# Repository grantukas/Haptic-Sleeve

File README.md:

# Haptic-Sleeve
Repository for the code used for the Haptic Sleeve Project!

Below is a brief description of the folders.

### CaseModels
Contains the 3D models that house the Haptic Sleeve PCB.

### ESP32 Code
Contains the Micropython code to run on the ESP32, along with Micropython firmware to flash (.bin file).

### Haptic Sleeve Testing Program
Contains the testing program and documentation for testing the Haptic Sleeve. The data extraction program (to convert log file data to CSV) also lives here.

### Learn To Write Code
Contains the code for the Learn To Write Software.

### Schematic+Board
Contains the schematic and board layout files for the Haptic Sleeve.

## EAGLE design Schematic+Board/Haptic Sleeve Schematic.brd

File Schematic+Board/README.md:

## Schematic and board layout files
Schematic and board layout for the ESP32, 2 Sparkfun motor drivers.
Created in Autodesk Eagle.

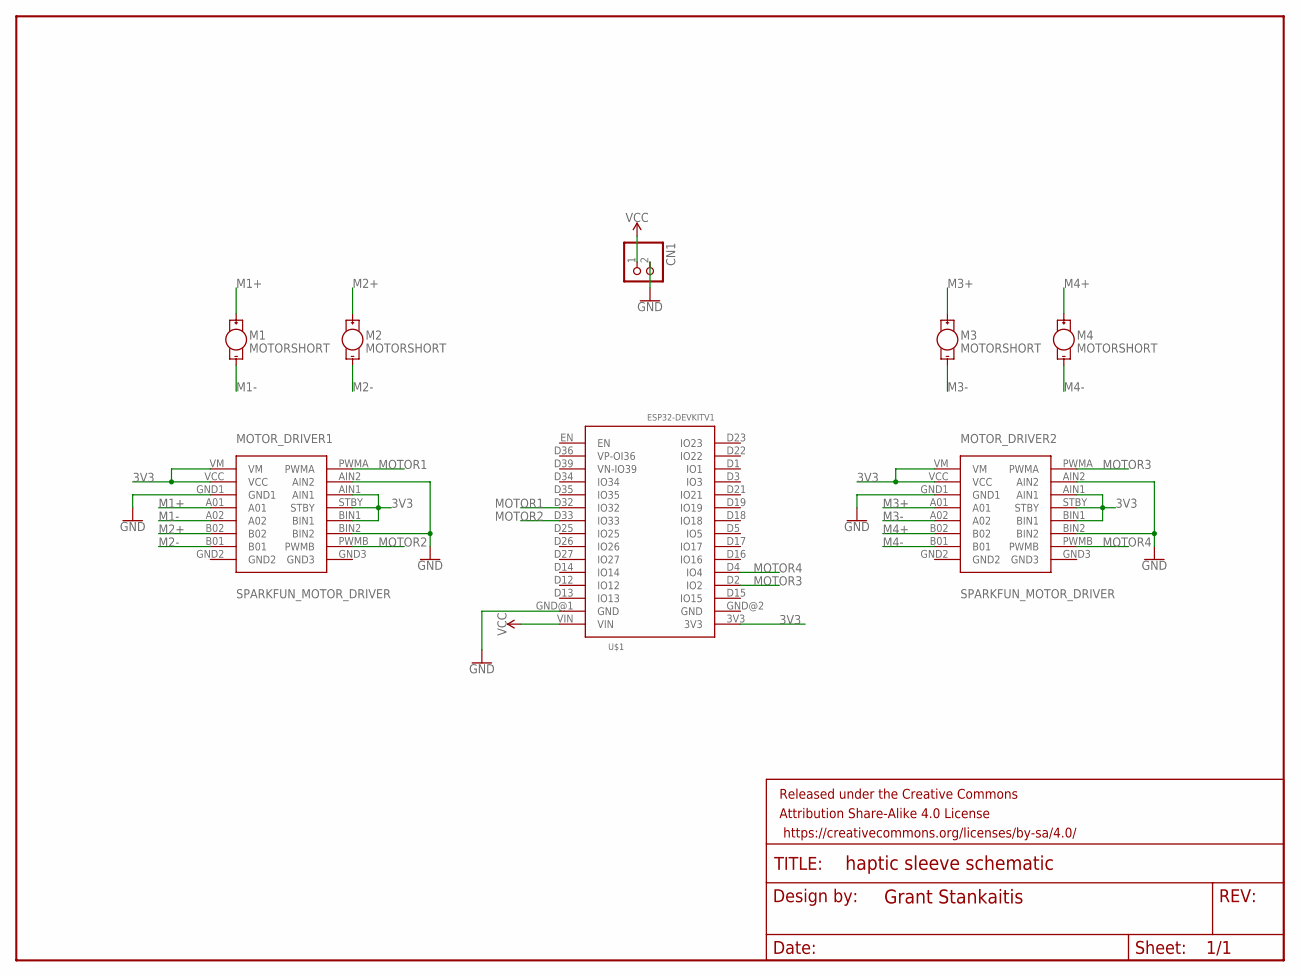
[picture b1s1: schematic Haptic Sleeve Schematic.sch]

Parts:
CN1: JST_2PIN-THM-RA; JST-PH-2-THM-RA
FRAME1: FRAME-LETTERNO_PACKAGE; DUMMY
M1, M2, M3, M4: MOTORSHORT; VIBE-MOTOR-10MM-SMD
MOTOR_DRIVER1, MOTOR_DRIVER2: SPARKFUN_MOTOR_DRIVER
U$1: ESP32DEVKITV1; ESP32-DEVKITV1

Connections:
3V3: MOTOR_DRIVER1.AIN1, MOTOR_DRIVER1.BIN1, MOTOR_DRIVER1.STBY, MOTOR_DRIVER1.VCC, MOTOR_DRIVER1.VM, MOTOR_DRIVER2.AIN1, MOTOR_DRIVER2.BIN1, MOTOR_DRIVER2.STBY, MOTOR_DRIVER2.VCC, MOTOR_DRIVER2.VM, U$1.3V3
GND: CN1.2 (1), MOTOR_DRIVER1.AIN2, MOTOR_DRIVER1.BIN2, MOTOR_DRIVER1.GND1, MOTOR_DRIVER2.AIN2, MOTOR_DRIVER2.BIN2, MOTOR_DRIVER2.GND1, U$1.GND@1 (GND)
M1+: M1.+, MOTOR_DRIVER1.A01
M1-: M1.-, MOTOR_DRIVER1.A02
M2+: M2.+, MOTOR_DRIVER1.B02
M2-: M2.-, MOTOR_DRIVER1.B01
M3+: M3.+, MOTOR_DRIVER2.A01
M3-: M3.-, MOTOR_DRIVER2.A02
M4+: M4.+, MOTOR_DRIVER2.B02
M4-: M4.-, MOTOR_DRIVER2.B01
MOTOR1: MOTOR_DRIVER1.PWMA, U$1.D32 (IO32)
MOTOR2: MOTOR_DRIVER1.PWMB, U$1.D33 (IO33)
MOTOR3: MOTOR_DRIVER2.PWMA, U$1.D2 (IO2)
MOTOR4: MOTOR_DRIVER2.PWMB, U$1.D4 (IO4)
VCC: CN1.1 (2), U$1.VIN

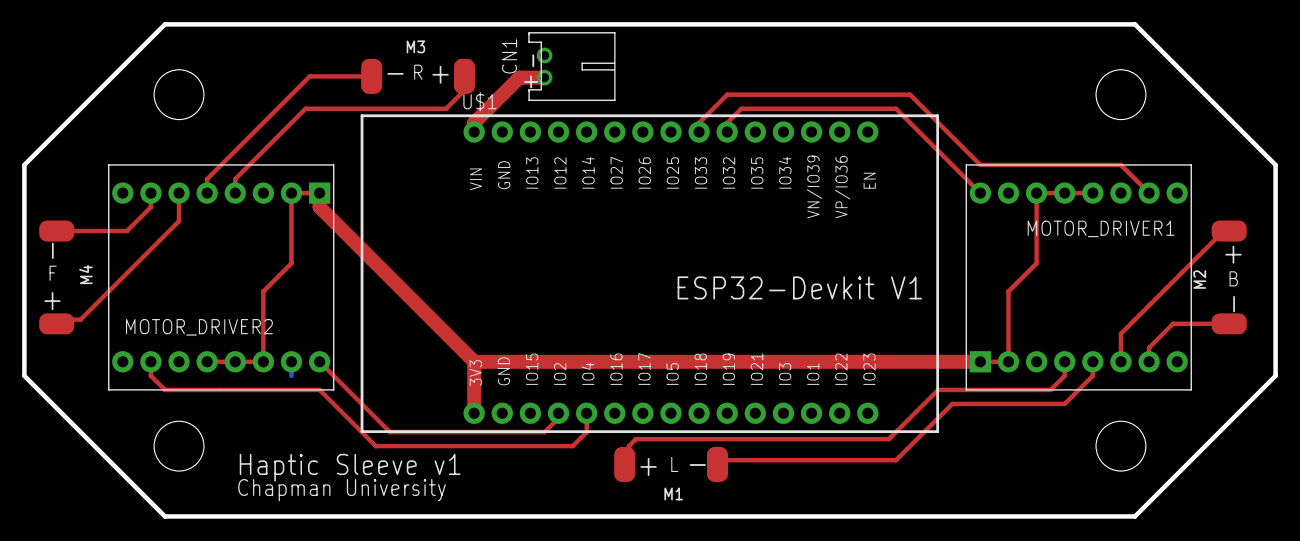
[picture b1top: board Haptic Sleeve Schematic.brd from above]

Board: 2 copper layers, 113.0 x 44.5 mm, 9 parts (0 on the bottom side), 15 nets.

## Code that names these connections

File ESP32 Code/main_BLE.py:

import bluetooth
import time
import machine
from machine import Pin
from bleuart import BLEUART

# Forward motor pin B, PWMB, pin 4
# Left motor pin A, PWMA, pin 34
# Back motor pin B, PWMB, pin 35
# Right motor pin A, PWMA, pin 2
motor1 = machine.PWM(Pin(4))
motor2 = machine.PWM(Pin(32))
motor3 = machine.PWM(Pin(33))
motor4 = machine.PWM(Pin(2))

motor1.freq(1000)
motor2.freq(1000)
motor3.freq(1000)
motor4.freq(1000)

motor1.duty(0)
motor2.duty(0)
motor3.duty(0)
motor4.duty(0)

forward = 0
left = 0
back = 0
right = 0

def start_sleeve():
    ble = bluetooth.BLE()
    uart = BLEUART(ble)
 
    def set_PWM():
      # Read and decode data sent over BLE UART
      rx_payload = uart.read().decode().strip()
      
      # Split the formatted payload for direction and range
      # Assumes that sent messages are formatted properly & non-empty
      direction, range = rx_payload.split(',')
      direction = int(direction)
      range = int(range)
      
      # Range comes in 0, 1, 2, 3
      # Duty is 1/3 of the max, ie. 33.33%, 66.33%, 100%
      # Max for PWM is 1023, 341 is 1/3 *1023
      duty = int(range*341)
      
      # Assign duty based on direction
      if direction == 1:
        forward = duty
        left = 0
        back = 0
        right = 0
      elif direction == 2:
        forward = 0
        left = duty
        back = 0
        right = 0
      elif direction == 3:
        forward = 0
        left = 0
        back = duty
        right = 0
      elif direction == 4:
        forward = 0
        left = 0
        back = 0
        right = duty
      else: # Set all to 0
        forward = 0
        left = 0
        back = 0
        right = 0
      
      # Set duty
      motor1.duty(forward)
      motor2.duty(left)
      motor3.duty(back)
      motor4.duty(right)
    
    # Set callback for BLE event
    # Callbacks triggered immediately when new payload received
    uart.irq(handler = set_PWM)

    try:
      while True: # Infinite loop, sleep used as a placeholder
        time.sleep_ms(1)
    except KeyboardInterrupt:
      pass

    # Close the BLE UART connection
    uart.close()

if __name__ == "__main__":
    start_sleeve()


    

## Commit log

2020-06-26 Rename main.py to mainORIGINAL.py
2020-06-26 Rename boot.py to bootORIGINAL.py
2020-06-26 Rename boot1.py to boot.py
2020-06-26 HERE FOR EARLIER TESTING
2020-06-26 Main code for ESP32
2020-06-26 Boot code for ESP32
2020-06-30 Updated from v1
    Updated from v1 with supports for motor mounts and extra height to accommodate for the ESP32 sitting on female headers in the PCB.
2020-07-17 Updated user training
2020-08-13 Added extra debug line
    Added the line "logging.debug("Key pressed: b'0'")" in run_test. This one line helps out the data extraction program, continues the trend of 3 lines of data to allow the data extraction program to pr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
2020-08-13 Added data extraction program

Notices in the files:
parts and their libraries:
SparkFun-Aesthetics: Licensing: Creative Commons ShareAlike 4.0 International - https://creativecommons.org/licenses/by-sa/4.0
SparkFun-Aesthetics: Released under the Creative Commons Attribution Share-Alike 4.0 License
SparkFun-Aesthetics: https://creativecommons.org/licenses/by-sa/4.0
